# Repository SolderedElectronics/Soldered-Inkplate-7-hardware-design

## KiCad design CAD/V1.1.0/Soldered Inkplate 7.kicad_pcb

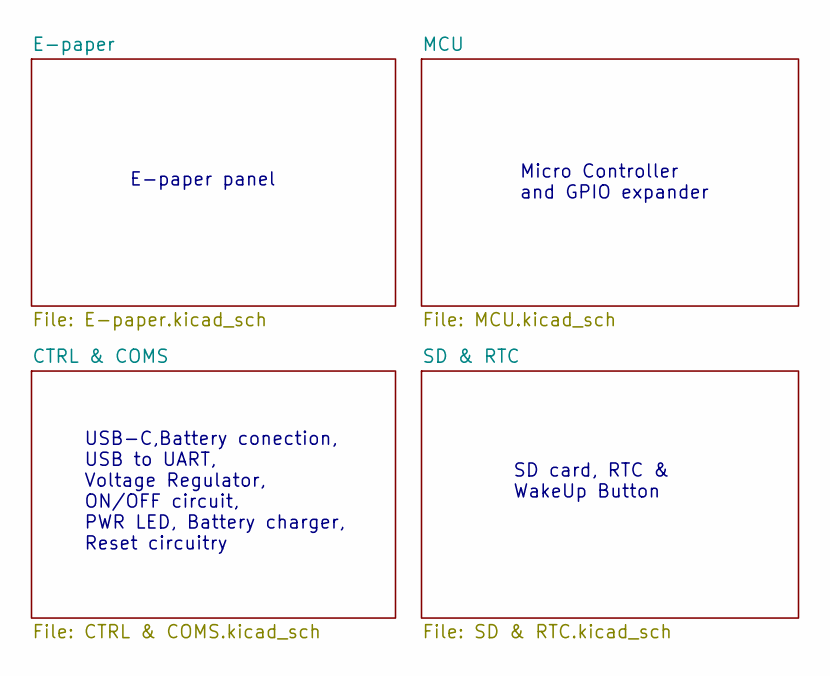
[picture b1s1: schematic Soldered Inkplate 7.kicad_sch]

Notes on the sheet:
E-paper panel
USB-C,Battery conection, USB to UART, Voltage Regulator, ON/OFF circuit, PWR LED, Battery charger, Reset circuitry
Micro Controller and GPIO expander
SD card, RTC & WakeUp Button

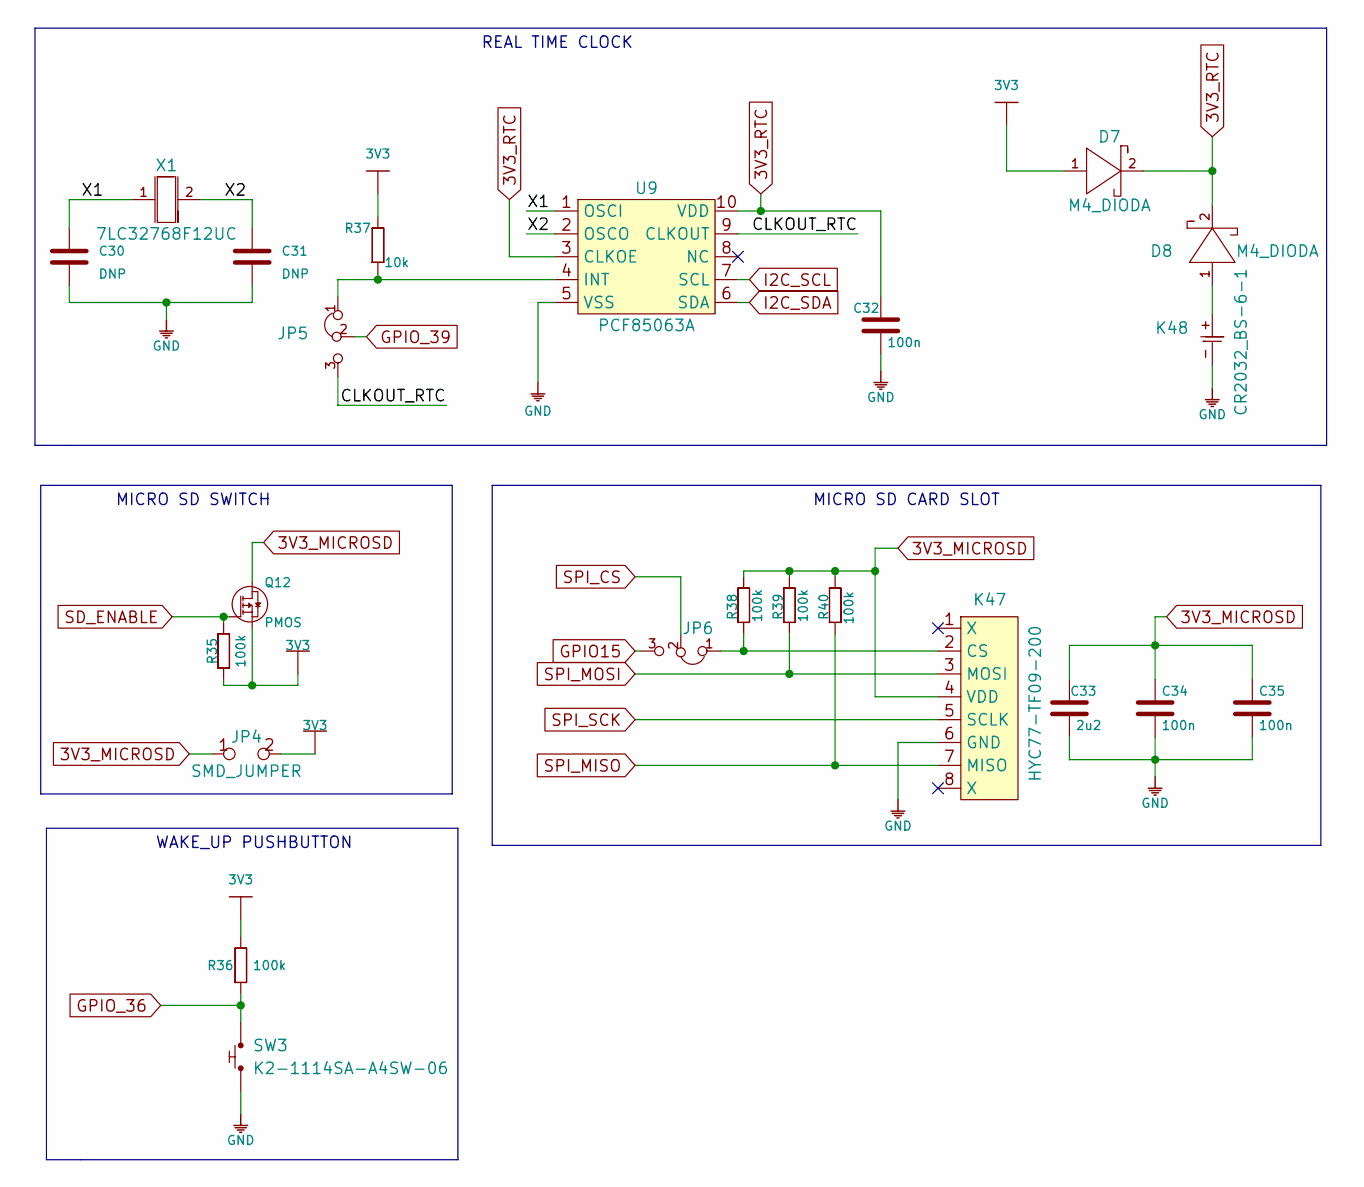
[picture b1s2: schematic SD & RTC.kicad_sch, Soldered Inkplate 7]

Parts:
C30, C31: DNP; 0603C
C32, C34, C35: 100n; 0603C
C33: 2u2; 0603C
D7, D8: M4_DIODA
JP4: SMD_JUMPER
JP5, JP6: SMD_JUMPER_3_PAD_CONNECTED_LEFT_TRACE
K47: HYC77-TF09-200
K48: CR2032_BS-6-1; CR2032-BS-6-1
Q12: PMOS; SOT-23-3
R35, R36, R38, R39, R40: 100k; 0603R
R37: 10k; 0603R
SW3: K2-1114SA-A4SW-06
U9: PCF85063A
X1: 7LC32768F12UC; ABS07AIG-32.768KHZ-7-D-T

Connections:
3V3: D7.1 (A), JP4.2, Q12.2 (S), R35.1, R36.2, R37.2; also elsewhere on the board
3V3_MICROSD: C33.2, C34.2, C35.2, JP4.1, K47.4 (VDD), Q12.3 (D), R38.2, R39.2, R40.2
3V3_RTC: C32.2, D7.2 (K), D8.2 (K), U9.3 (CLKOE), U9.10 (VDD)
/SD & RTC/CLKOUT_RTC: JP5.3, U9.9 (CLKOUT)
/SD & RTC/X1: C30.2, U9.1 (OSCI), X1.1
/SD & RTC/X2: C31.2, U9.2 (OSCO), X1.2
GND: C30.1, C31.1, C32.1, C33.1, C34.1, C35.1, K47.6 (GND), K48.-, SW3.1, U9.5 (VSS); also elsewhere on the board
GPIO15: JP6.3; also elsewhere on the board
GPIO_36: R36.1, SW3.2; also elsewhere on the board
GPIO_39: JP5.2; also elsewhere on the board
I2C_SCL: U9.7 (SCL); also elsewhere on the board
I2C_SDA: U9.6 (SDA); also elsewhere on the board
unnamed: D8.1 (A), K48.+
unnamed: JP5.1, R37.1, U9.4 (INT)
unnamed: JP6.1, K47.2 (CS), R38.1
SD_ENABLE: Q12.1 (G), R35.2; also elsewhere on the board
SPI_CS: JP6.2; also elsewhere on the board
SPI_MISO: K47.7 (MISO), R40.1; also elsewhere on the board
SPI_MOSI: K47.3 (MOSI), R39.1; also elsewhere on the board
SPI_SCK: K47.5 (SCLK); also elsewhere on the board

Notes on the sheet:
MICRO SD CARD SLOT
REAL TIME CLOCK
WAKE_UP PUSHBUTTON
MICRO SD SWITCH

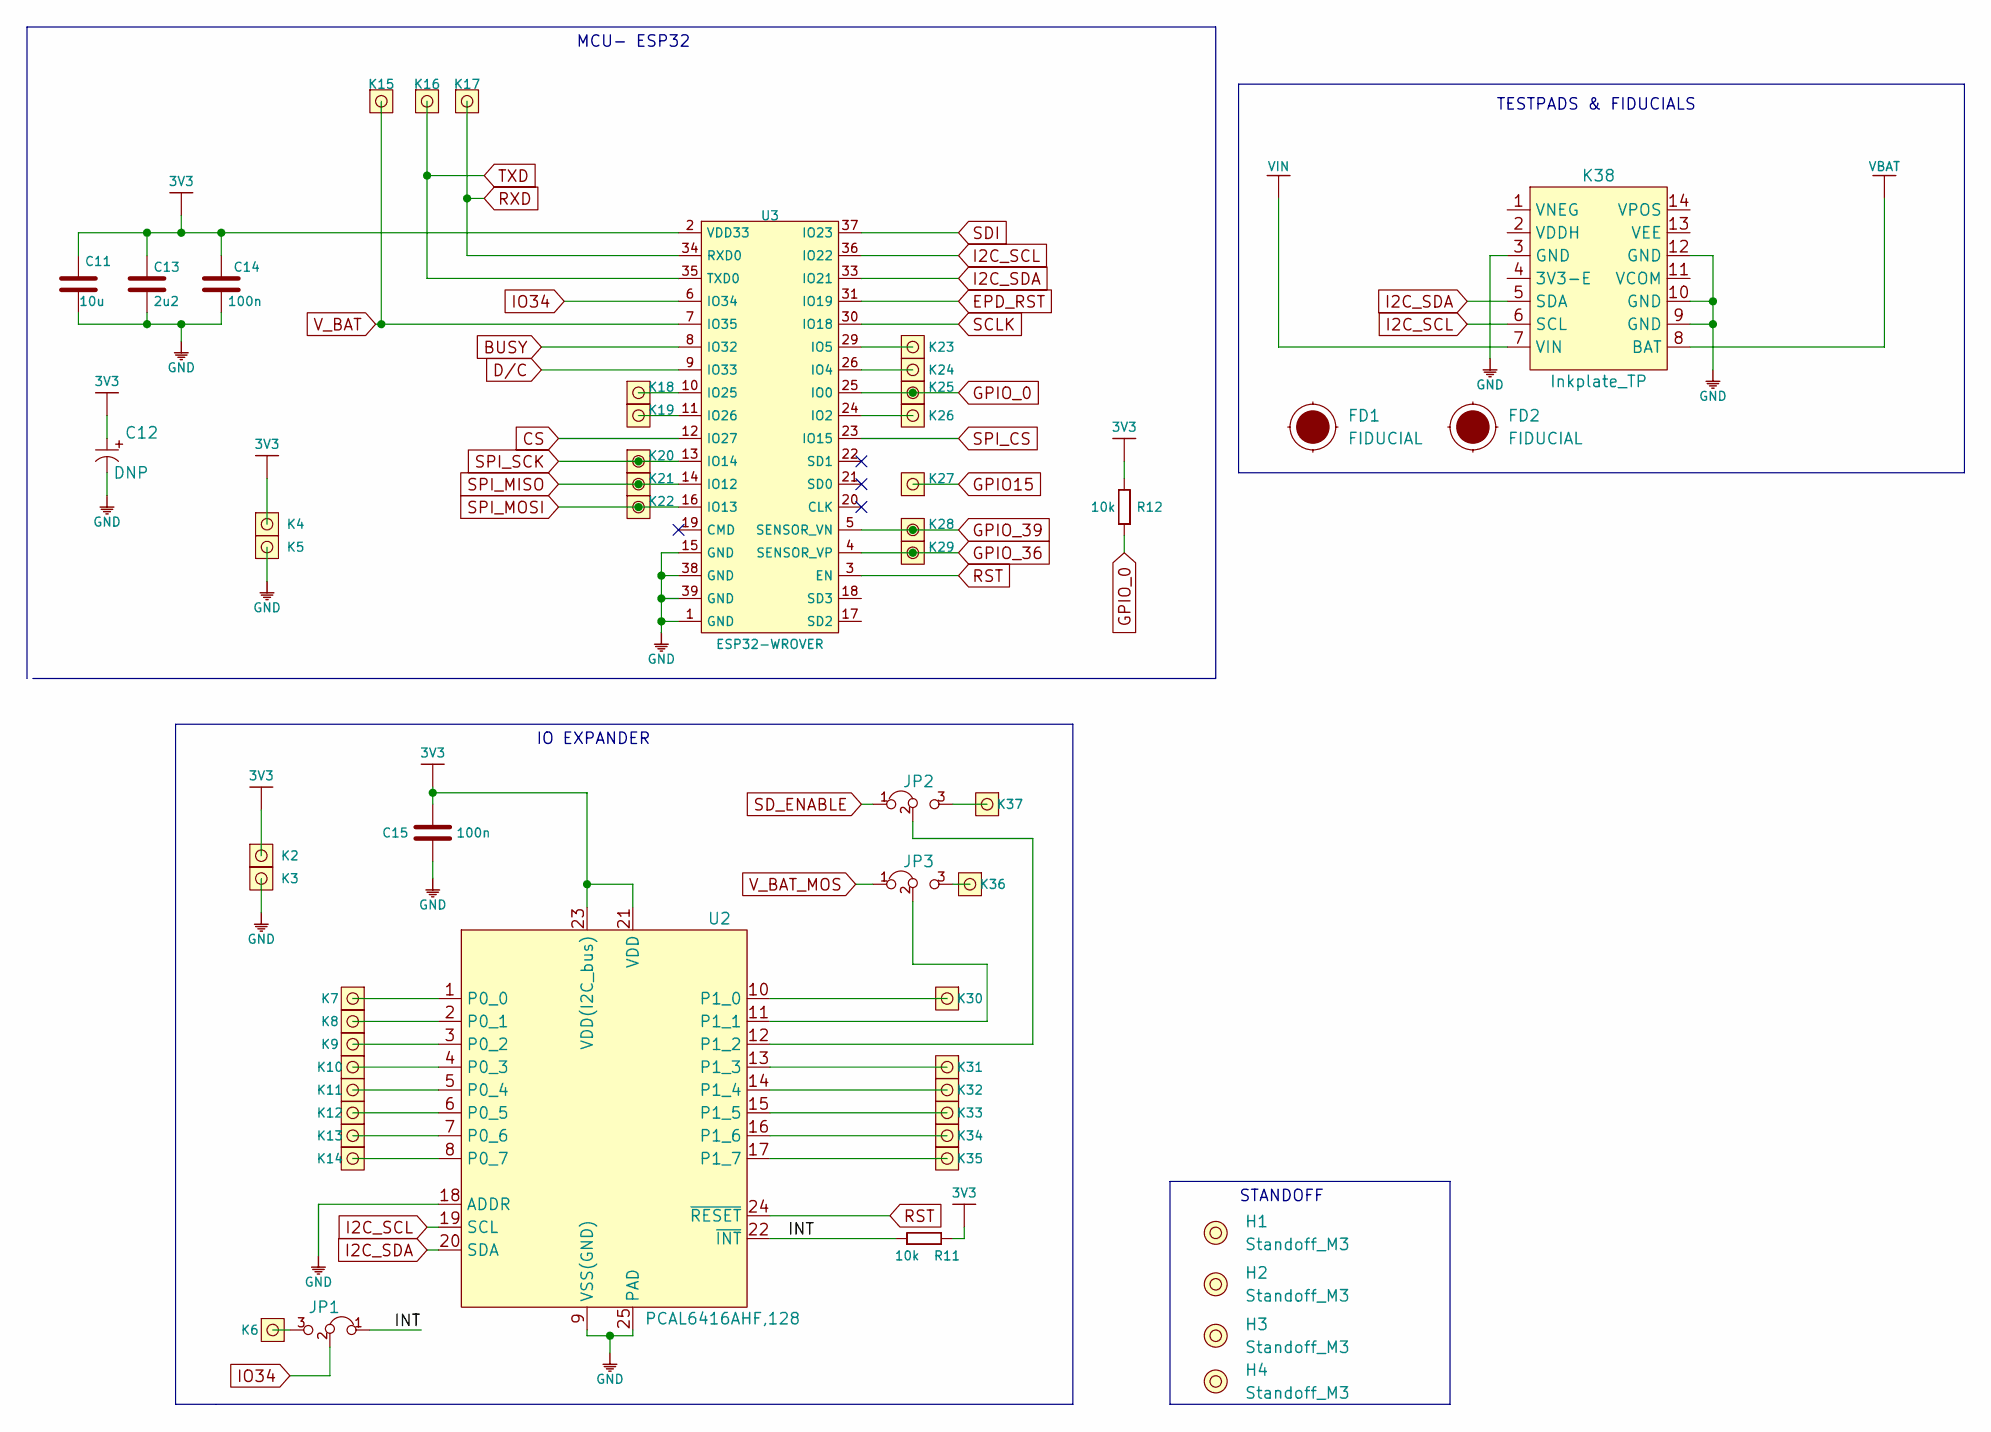
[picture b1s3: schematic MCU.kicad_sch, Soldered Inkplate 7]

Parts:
C11: 10u; 1206C
C12: DNP; 2917C
C13: 2u2; 0603C
C14, C15: 100n; 0603C
FD1, FD2: FIDUCIAL; FIDUCIAL_23
H1, H2, H3, H4: Standoff_M3
JP1, JP2, JP3: SMD_JUMPER_3_PAD_CONNECTED_LEFT_TRACE
K2, K3, K4, K5, K6, K7, K8, K9, K10, K11, K12, K13, K14, K15, K16, K17, K18, K19, K20, K21, K22, K23, K24, K25, K26, K27, K28, K29, K30, K31, K32, K33, K34, K35, K36, K37: HEADER_MALE_1X1_Inkplate
K38: Inkplate_TP; INKPLATE TEST HEADER
R11, R12: 10k; 0603R
U2: PCAL6416AHF,128
U3: ESP32-WROVER

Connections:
3V3: C11.2, C12.1 (+), C13.2, C14.2, C15.2, K2.1, K4.1, R11.1, R12.2, U2.21 (VDD), U2.23 (VDD(I2C_bus)), U3.2 (VDD33); also elsewhere on the board
/MCU/INT: JP1.1, R11.2, U2.22 (~INT)
BUSY: U3.8 (IO32); also elsewhere on the board
CS: U3.12 (IO27); also elsewhere on the board
D/C: U3.9 (IO33); also elsewhere on the board
EPD_RST: U3.31 (IO19); also elsewhere on the board
GND: C11.1, C12.2 (-), C13.1, C14.1, C15.1, K3.1, K5.1, K38.3 (GND), K38.9 (GND), K38.10 (GND), K38.12 (GND), U2.9 (VSS(GND)), U2.18 (ADDR), U2.25 (PAD), U3.1 (GND), U3.15 (GND), U3.38 (GND), U3.39 (GND); also elsewhere on the board
GPIO15: K27.1; also elsewhere on the board
GPIO_0: K25.1, R12.1, U3.25 (IO0); also elsewhere on the board
GPIO_36: K29.1, U3.4 (SENSOR_VP); also elsewhere on the board
GPIO_39: K28.1, U3.5 (SENSOR_VN); also elsewhere on the board
I2C_SCL: K38.6 (SCL), U2.19 (SCL), U3.36 (IO22); also elsewhere on the board
I2C_SDA: K38.5 (SDA), U2.20 (SDA), U3.33 (IO21); also elsewhere on the board
IO34: JP1.2, U3.6 (IO34)
unnamed: JP1.3, K6.1
unnamed: JP2.2, U2.12 (P1_2)
unnamed: JP2.3, K37.1
unnamed: JP3.2, U2.11 (P1_1)
unnamed: JP3.3, K36.1
unnamed: K7.1, U2.1 (P0_0)
unnamed: K8.1, U2.2 (P0_1)
unnamed: K9.1, U2.3 (P0_2)
unnamed: K10.1, U2.4 (P0_3)
unnamed: K11.1, U2.5 (P0_4)
unnamed: K12.1, U2.6 (P0_5)
unnamed: K13.1, U2.7 (P0_6)
unnamed: K14.1, U2.8 (P0_7)
unnamed: K18.1, U3.10 (IO25)
unnamed: K19.1, U3.11 (IO26)
unnamed: K23.1, U3.29 (IO5)
unnamed: K24.1, U3.26 (IO4)
unnamed: K26.1, U3.24 (IO2)
unnamed: K30.1, U2.10 (P1_0)
unnamed: K31.1, U2.13 (P1_3)
unnamed: K32.1, U2.14 (P1_4)
unnamed: K33.1, U2.15 (P1_5)
unnamed: K34.1, U2.16 (P1_6)
unnamed: K35.1, U2.17 (P1_7)
RST: U2.24 (~RESET), U3.3 (EN); also elsewhere on the board
RXD: K17.1, U3.34 (RXD0); also elsewhere on the board
SCLK: U3.30 (IO18); also elsewhere on the board
SDI: U3.37 (IO23); also elsewhere on the board
SD_ENABLE: JP2.1; also elsewhere on the board
SPI_CS: U3.23 (IO15); also elsewhere on the board
SPI_MISO: K21.1, U3.14 (IO12); also elsewhere on the board
SPI_MOSI: K22.1, U3.16 (IO13); also elsewhere on the board
SPI_SCK: K20.1, U3.13 (IO14); also elsewhere on the board
TXD: K16.1, U3.35 (TXD0); also elsewhere on the board
VBAT: K38.8 (BAT); also elsewhere on the board
VIN: K38.7 (VIN); also elsewhere on the board
V_BAT: K15.1, U3.7 (IO35); also elsewhere on the board
V_BAT_MOS: JP3.1; also elsewhere on the board

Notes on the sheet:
STANDOFF
IO EXPANDER
MCU- ESP32
TESTPADS & FIDUCIALS

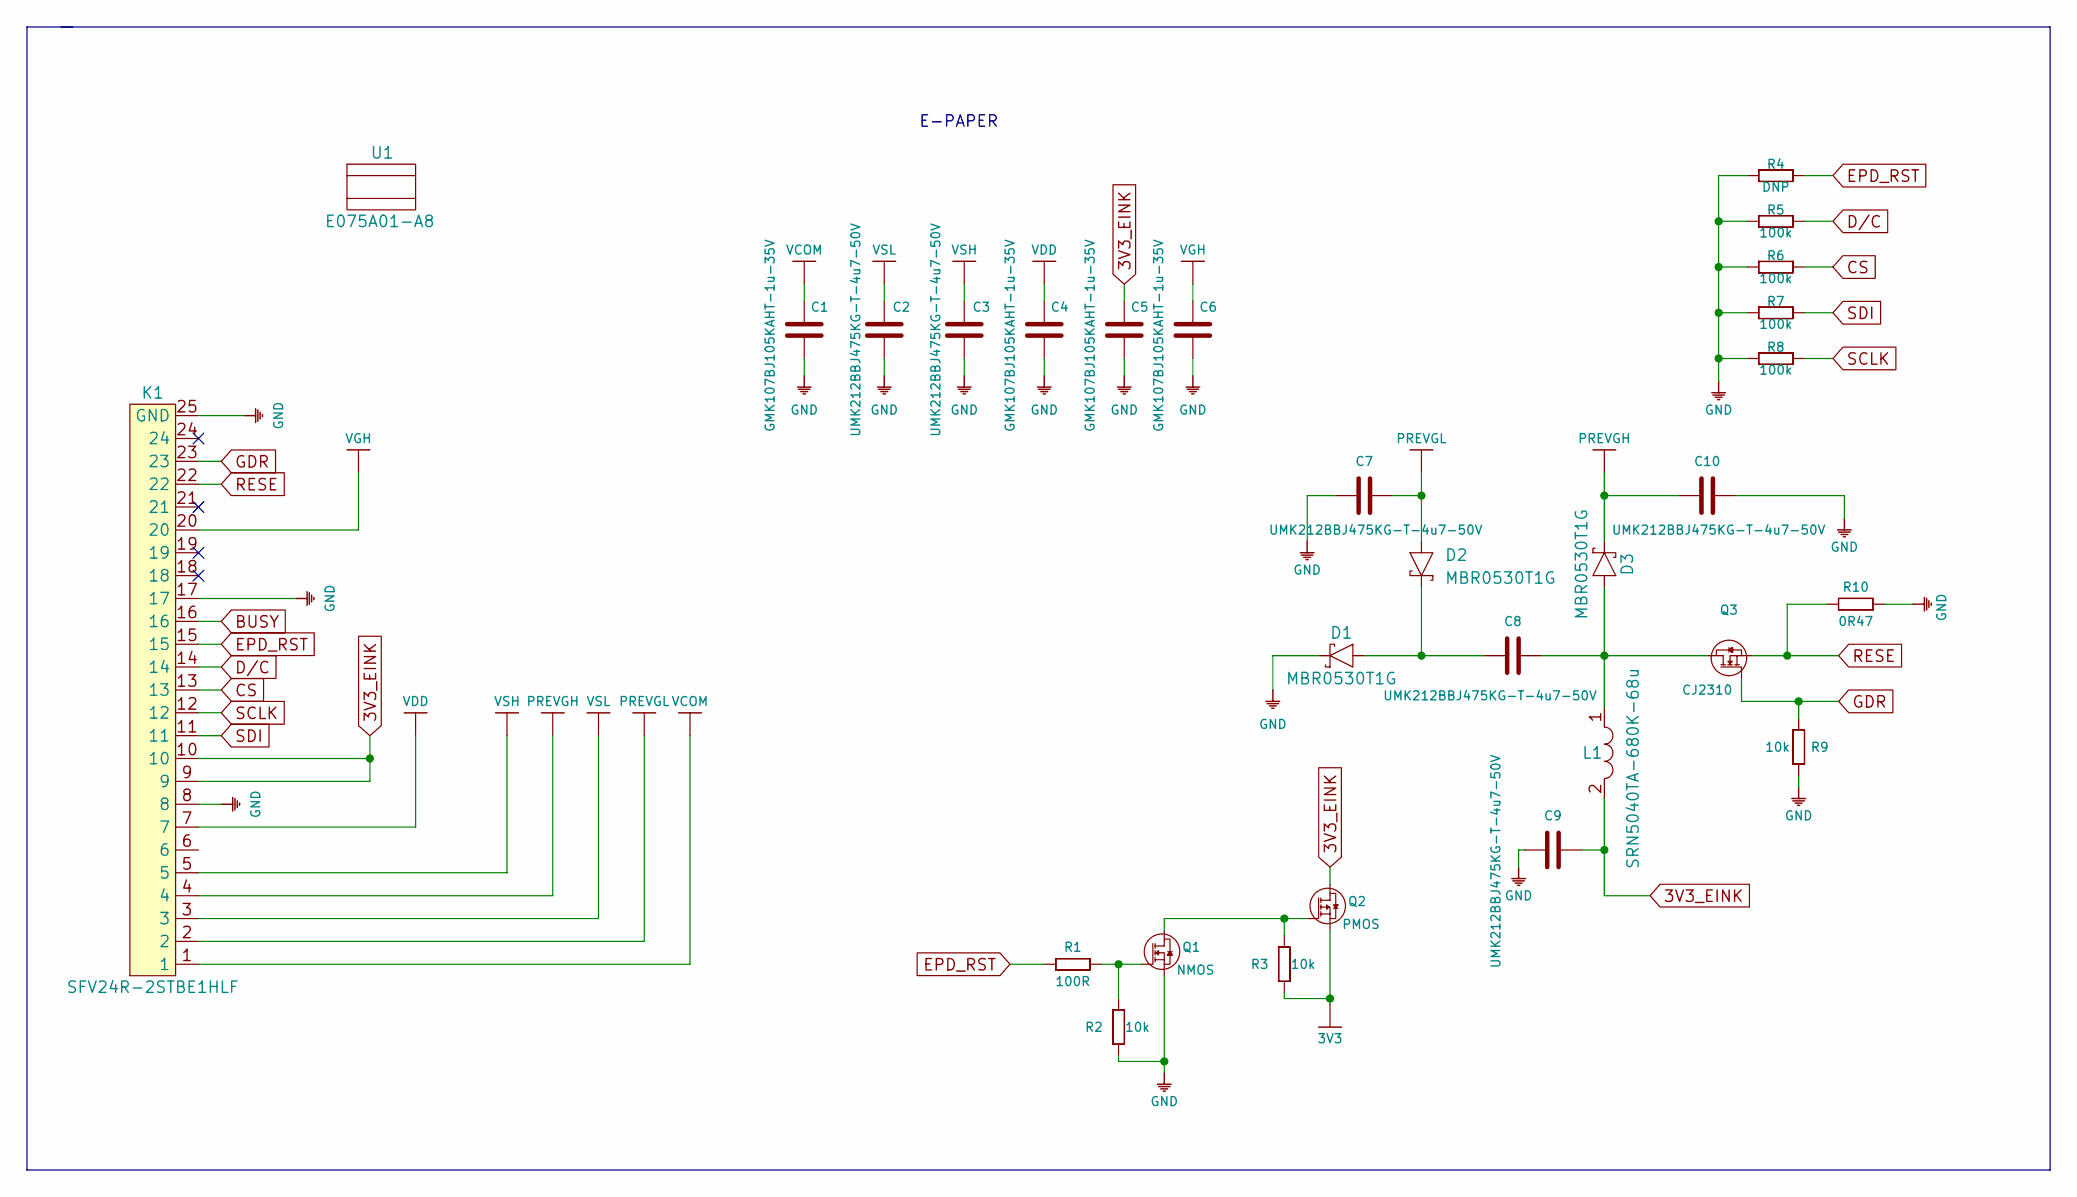
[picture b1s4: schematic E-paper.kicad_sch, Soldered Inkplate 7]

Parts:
C1, C4, C5, C6: GMK107BJ105KAHT-1u-35V; 0603C
C2, C3, C7, C8, C9, C10: UMK212BBJ475KG-T-4u7-50V; 0805C
D1, D2, D3: MBR0530T1G; SOD−123
K1: SFV24R-2STBE1HLF
L1: SRN5040TA-680K-68u; SRN5040TA-680K
Q1: NMOS; SOT-23-3
Q2: PMOS; SOT-23-3
Q3: CJ2310; SOT-23-3
R1: 100R; 0603R
R2, R3, R9: 10k; 0603R
R4: DNP; 0603R
R5, R6, R7, R8: 100k; 0603R
R10: 0R47; 0603R
U1: E075A01-A8

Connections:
3V3: Q2.2 (S), R3.1; also elsewhere on the board
3V3_EINK: C5.2, C9.2, K1.9, K1.10, L1.2, Q2.3 (D)
BUSY: K1.16; also elsewhere on the board
CS: K1.13, R6.2; also elsewhere on the board
D/C: K1.14, R5.2; also elsewhere on the board
EPD_RST: K1.15, R1.1, R4.2; also elsewhere on the board
GDR: K1.23, Q3.1 (G), R9.2
GND: C1.1, C2.1, C3.1, C4.1, C5.1, C6.1, C7.1, C9.1, C10.2, D1.1 (C), K1.8, K1.17, K1.25 (GND), Q1.2 (S), R2.1, R4.1, R5.1, R6.1, R7.1, R8.1, R9.1, R10.1; also elsewhere on the board
unnamed: C8.1, D1.2 (A), D2.1 (C)
unnamed: C8.2, D3.2 (A), L1.1, Q3.3 (D)
unnamed: Q1.1 (G), R1.2, R2.2
unnamed: Q1.3 (D), Q2.1 (G), R3.2
PREVGH: C10.1, D3.1 (C), K1.4
PREVGL: C7.2, D2.2 (A), K1.2
RESE: K1.22, Q3.2 (S), R10.2
SCLK: K1.12, R8.2; also elsewhere on the board
SDI: K1.11, R7.2; also elsewhere on the board
VCOM: C1.2, K1.1
VDD: C4.2, K1.7
VGH: C6.2, K1.20
VSH: C3.2, K1.5
VSL: C2.2, K1.3

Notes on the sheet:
E-PAPER

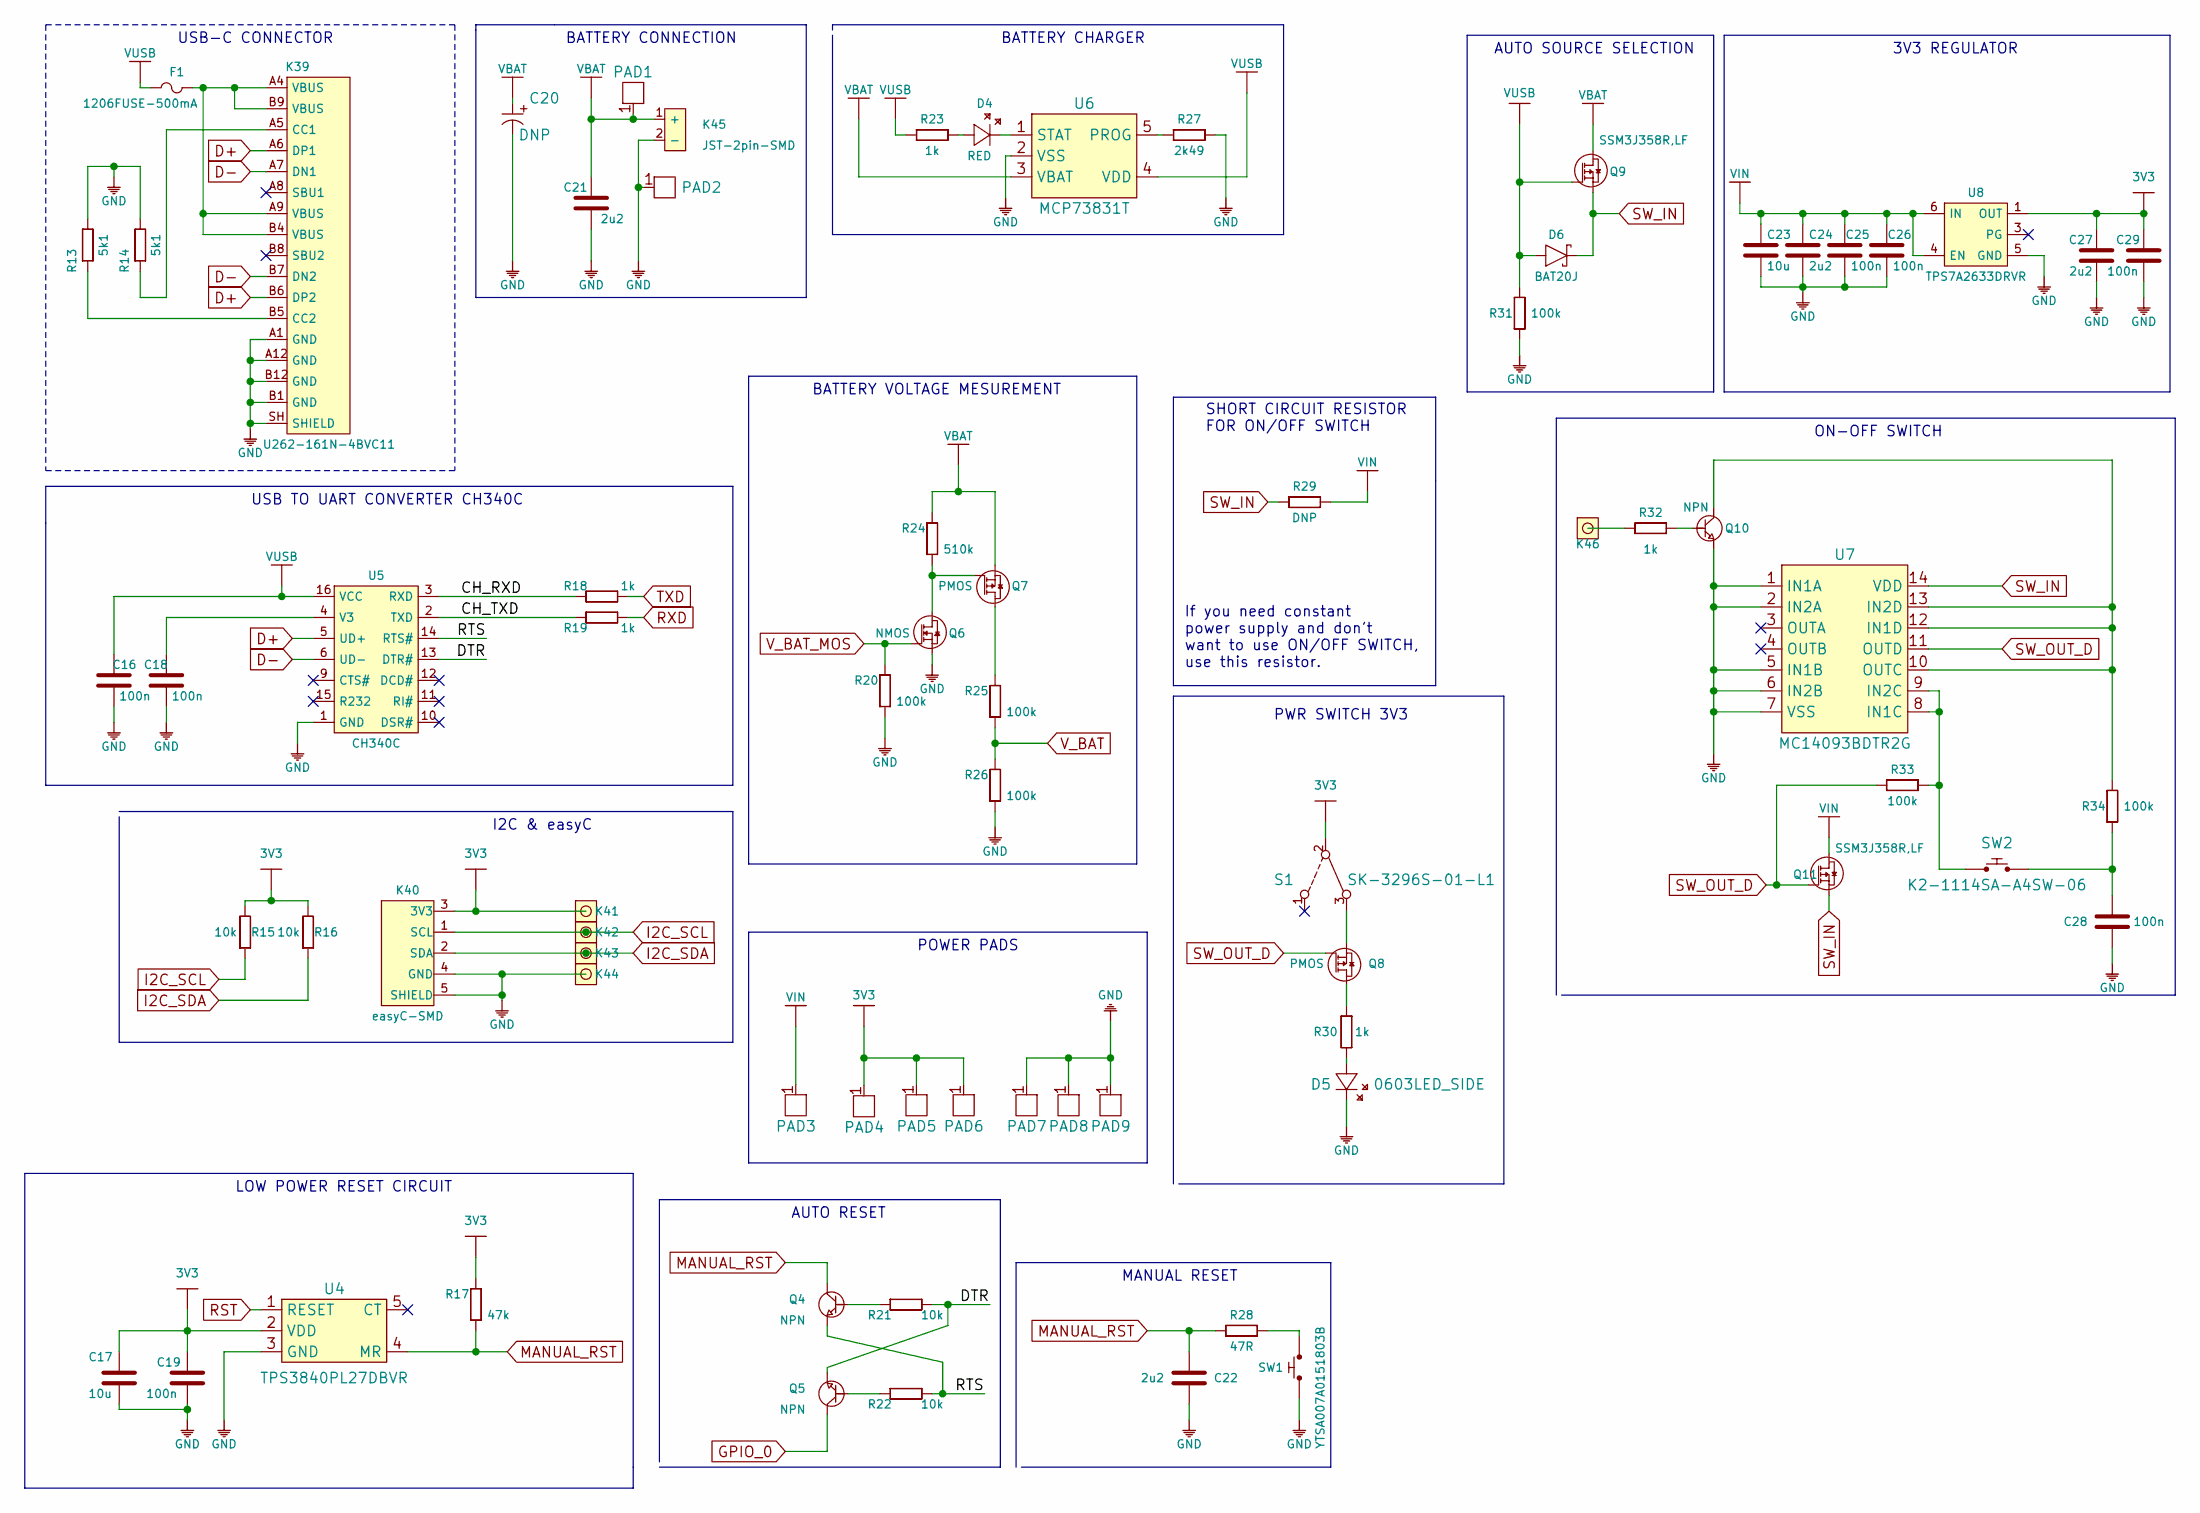
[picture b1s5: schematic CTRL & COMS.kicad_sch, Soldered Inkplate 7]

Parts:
C16, C18, C19, C25, C26, C28, C29: 100n; 0603C
C17, C23: 10u; 1206C
C20: DNP; 2917C
C21, C22, C24, C27: 2u2; 0603C
D4: RED; 0402LED
D5: 0603LED_SIDE; LTST-S270GKT
D6: BAT20J; SOD-323
F1: 1206FUSE-500mA; 1206FUSE
K39: U262-161N-4BVC11
K40: easyC-SMD; easyC-connector
K41, K42, K43, K44, K46: HEADER_MALE_1X1_Inkplate
K45: JST-2pin-SMD
PAD1, PAD2, PAD3, PAD4, PAD5, PAD6, PAD7, PAD8, PAD9: PAD_4x4
Q4, Q5, Q10: NPN; SOT-23-3
Q6: NMOS; SOT-23-3
Q7, Q8: PMOS; SOT-23-3
Q9, Q11: SSM3J358R,LF; SOT-23-3
R13, R14: 5k1; 0603R
R15, R16, R21, R22: 10k; 0603R
R17: 47k; 0603R
R18, R19, R23, R30, R32: 1k; 0603R
R20, R25, R26, R31, R33, R34: 100k; 0603R
R24: 510k; 0603R
R27: 2k49; 0603R
R28: 47R; 0603R
R29: DNP; 0603R
S1: SK-3296S-01-L1
SW1: YTSA007A0151803B
SW2: K2-1114SA-A4SW-06
U4: TPS3840PL27DBVR; SOT-23-5
U5: CH340C; SOP-16
U6: MCP73831T; SOT-23-5
U7: MC14093BDTR2G; TSSOP-14
U8: TPS7A2633DRVR

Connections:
3V3: C17.2, C19.2, C27.2, C29.2, K40.3 (3V3), K41.1, PAD4.1, PAD5.1, PAD6.1, R15.2, R16.2, R17.2, S1.2, U4.2 (VDD), U8.1 (OUT); also elsewhere on the board
/CTRL & COMS/CH_RXD: R18.1, U5.3 (RXD)
/CTRL & COMS/CH_TXD: R19.1, U5.2 (TXD)
/CTRL & COMS/DTR: Q5.2 (E), R21.2, U5.13 (DTR#)
/CTRL & COMS/RTS: Q4.2 (E), R22.2, U5.14 (RTS#)
D+: K39.A6 (DP1), K39.B6 (DP2), U5.5 (UD+)
D-: K39.A7 (DN1), K39.B7 (DN2), U5.6 (UD-)
GND: C16.1, C17.1, C18.1, C19.1, C20.2 (-), C21.1, C22.1, C23.1, C24.1, C25.1, C26.1, C27.1, C28.1, C29.1, D5.2 (K), K39.A1 (GND), K39.A12 (GND), K39.B1 (GND), K39.B12 (GND), K39.SH (SHIELD), K40.4 (GND), K40.5 (SHIELD), K44.1, K45.2 (-), PAD2.1, PAD7.1, PAD8.1, PAD9.1, Q6.2 (S), Q10.2 (E), R13.2, R14.2, R20.1, R26.1, R27.2, R31.1, SW1.1, U4.3 (GND), U5.1 (GND), U6.2 (VSS), U7.1 (IN1A), U7.2 (IN2A), U7.5 (IN1B), U7.6 (IN2B), U7.7 (VSS), U8.5 (GND); also elsewhere on the board
GPIO_0: Q5.3 (C); also elsewhere on the board
I2C_SCL: K40.1 (SCL), K42.1, R15.1; also elsewhere on the board
I2C_SDA: K40.2 (SDA), K43.1, R16.1; also elsewhere on the board
MANUAL_RST: C22.2, Q4.3 (C), R17.1, R28.2, U4.4 (MR)
unnamed: C18.2, U5.4 (V3)
unnamed: C28.2, R34.1, SW2.2
unnamed: D4.1 (A), R23.2
unnamed: D4.2 (K), U6.1 (STAT)
unnamed: D5.1 (A), R30.2
unnamed: F1.2, K39.A4 (VBUS), K39.A9 (VBUS), K39.B4 (VBUS), K39.B9 (VBUS)
unnamed: K39.A5 (CC1), R14.1
unnamed: K39.B5 (CC2), R13.1
unnamed: K46.1, R32.2
unnamed: Q4.1 (B), R21.1
unnamed: Q5.1 (B), R22.1
unnamed: Q6.3 (D), Q7.1 (G), R24.1
unnamed: Q7.3 (D), R25.2
unnamed: Q8.2 (S), S1.3
unnamed: Q8.3 (D), R30.1
unnamed: Q10.1 (B), R32.1
unnamed: Q10.3 (C), R34.2, U7.10 (OUTC), U7.12 (IN1D), U7.13 (IN2D)
unnamed: R27.1, U6.5 (PROG)
unnamed: R28.1, SW1.2
unnamed: R33.1, SW2.1, U7.8 (IN1C), U7.9 (IN2C)
RST: U4.1 (RESET); also elsewhere on the board
RXD: R19.2; also elsewhere on the board
SW_IN: D6.2 (C), Q9.2 (S), Q11.2 (S), R29.1, U7.14 (VDD)
SW_OUT_D: Q8.1 (G), Q11.1 (G), R33.2, U7.11 (OUTD)
TXD: R18.2; also elsewhere on the board
VBAT: C20.1 (+), C21.2, K45.1 (+), PAD1.1, Q7.2 (S), Q9.3 (D), R24.2, U6.3 (VBAT); also elsewhere on the board
VIN: C23.2, C24.2, C25.2, C26.2, PAD3.1, Q11.3 (D), R29.2, U8.4 (EN), U8.6 (IN); also elsewhere on the board
VUSB: C16.2, D6.1 (A), F1.1, Q9.1 (G), R23.1, R31.2, U5.16 (VCC), U6.4 (VDD)
V_BAT: R25.1, R26.2; also elsewhere on the board
V_BAT_MOS: Q6.1 (G), R20.2; also elsewhere on the board

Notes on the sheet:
PWR SWITCH 3V3
MANUAL RESET
3V3 REGULATOR
USB-C CONNECTOR
POWER PADS
LOW POWER RESET CIRCUIT
SHORT CIRCUIT RESISTOR FOR ON/OFF SWITCH
ON-OFF SWITCH
If you need constant power supply and don't want to use ON/OFF SWITCH, use this resistor.
I2C & easyC
USB TO UART CONVERTER CH340C
BATTERY VOLTAGE MESUREMENT
AUTO SOURCE SELECTION
AUTO RESET
BATTERY CONNECTION
BATTERY CHARGER

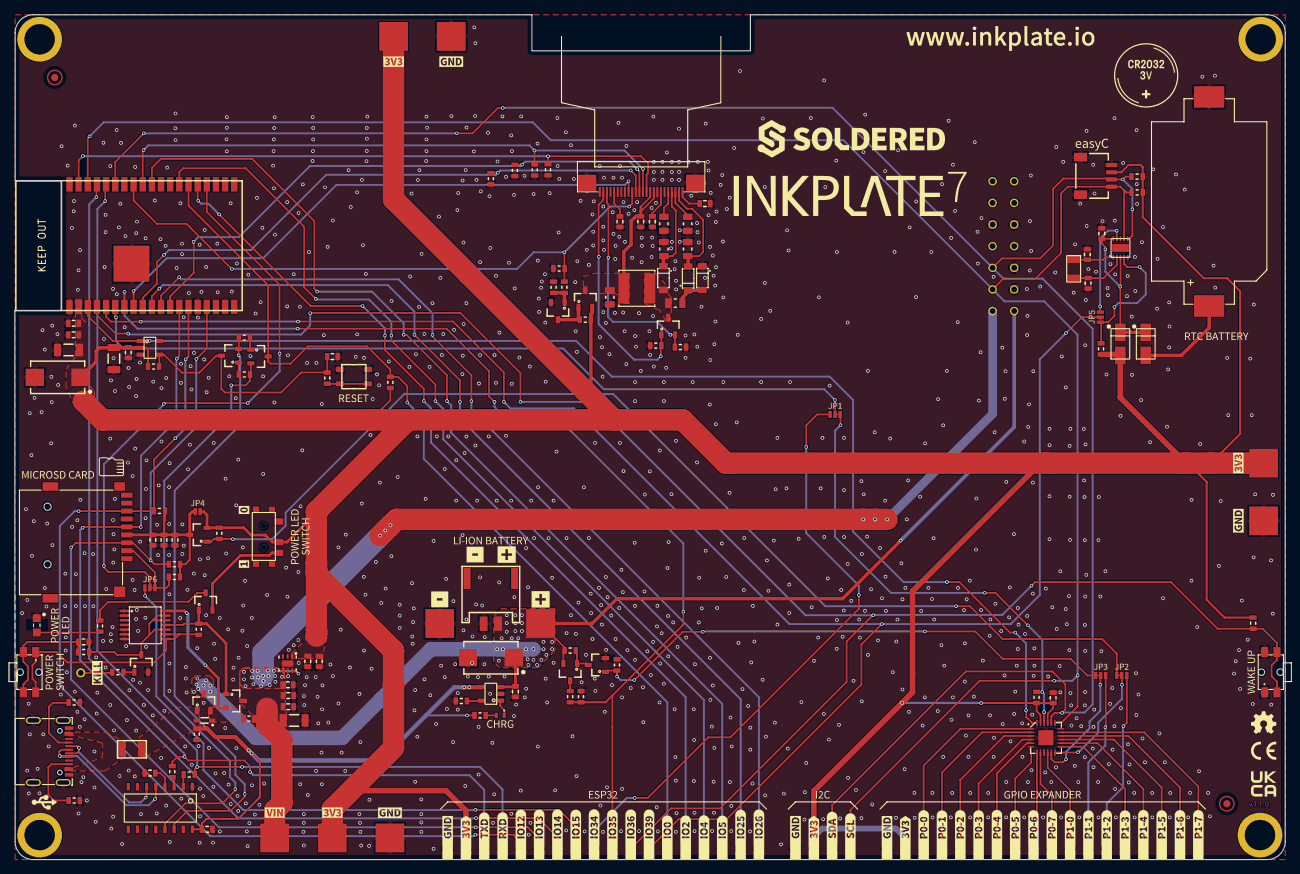
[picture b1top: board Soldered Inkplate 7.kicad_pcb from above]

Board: 2 copper layers, 176.2 x 117.2 mm, 257 parts (1 on the bottom side), 104 nets.

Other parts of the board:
Ref**: Val**; Version1.1.0
kibuzzard-63FC5BF8: G***; kibuzzard-63FC5BF8
kibuzzard-63FC5C0F: G***; kibuzzard-63FC5C0F
kibuzzard-63FC5C1D: G***; kibuzzard-63FC5C1D
kibuzzard-63FC5C04: G***; kibuzzard-63FC5C04
kibuzzard-63FC5C4F: G***; kibuzzard-63FC5C4F
kibuzzard-63FC5C5F: G***; kibuzzard-63FC5C5F
kibuzzard-63FC5C6B: G***; kibuzzard-63FC5C6B
kibuzzard-63FC5C7E: G***; kibuzzard-63FC5C7E
kibuzzard-63FC5C9A: G***; kibuzzard-63FC5C9A
kibuzzard-63FC5C17: G***; kibuzzard-63FC5C17
kibuzzard-63FC5C40: G***; kibuzzard-63FC5C40
kibuzzard-63FC5C46: G***; kibuzzard-63FC5C46
kibuzzard-63FC5C65: G***; kibuzzard-63FC5C65
kibuzzard-63FC5C84: G***; kibuzzard-63FC5C84
kibuzzard-63FC5C93: G***; kibuzzard-63FC5C93
kibuzzard-63FC5CA4: G***; kibuzzard-63FC5CA4
kibuzzard-63FC5CB5: G***; kibuzzard-63FC5CB5
kibuzzard-63FC5CBB: G***; kibuzzard-63FC5CBB
kibuzzard-63FC5CCD: G***; kibuzzard-63FC5CCD
kibuzzard-63FC5CD4: G***; kibuzzard-63FC5CD4
kibuzzard-63FC5CDA: G***; kibuzzard-63FC5CDA
kibuzzard-63FC5CE4: G***; kibuzzard-63FC5CE4
kibuzzard-63FC5CF6: G***; kibuzzard-63FC5CF6
kibuzzard-63FC5CFE: G***; kibuzzard-63FC5CFE
kibuzzard-63FC5D5D: G***; kibuzzard-63FC5D5D
kibuzzard-63FC5D6B: G***; kibuzzard-63FC5D6B
kibuzzard-63FC5D09: G***; kibuzzard-63FC5D09
kibuzzard-63FC5D13: G***; kibuzzard-63FC5D13
kibuzzard-63FC5D43: G***; kibuzzard-63FC5D43
kibuzzard-63FC5D64: G***; kibuzzard-63FC5D64
kibuzzard-63FC5D72: G***; kibuzzard-63FC5D72
kibuzzard-63FC5D84: G***; kibuzzard-63FC5D84
kibuzzard-63FC5D91: G***; kibuzzard-63FC5D91
kibuzzard-63FC5F9D: G***; kibuzzard-63FC5F9D
kibuzzard-63FC5F93: G***; kibuzzard-63FC5F93
kibuzzard-63FC5FB3: G***; kibuzzard-63FC5FB3
kibuzzard-63FC5FC1: G***; kibuzzard-63FC5FC1
kibuzzard-63FC5FCF: G***; kibuzzard-63FC5FCF
kibuzzard-63FC5FEC: G***; kibuzzard-63FC5FEC
kibuzzard-63FC5FF3: G***; kibuzzard-63FC5FF3
kibuzzard-63FC60AD: G***; kibuzzard-63FC60AD
kibuzzard-63FC60BC: G***; kibuzzard-63FC60BC
kibuzzard-63FC60D1: G***; kibuzzard-63FC60D1
kibuzzard-63FC60DF: G***; kibuzzard-63FC60DF
kibuzzard-63FC60EF: G***; kibuzzard-63FC60EF
kibuzzard-63FC60FE: G***; kibuzzard-63FC60FE
kibuzzard-63FC604C: G***; kibuzzard-63FC604C
kibuzzard-63FC605A: G***; kibuzzard-63FC605A
kibuzzard-63FC607B: G***; kibuzzard-63FC607B
kibuzzard-63FC609F: G***; kibuzzard-63FC609F
kibuzzard-63FC610B: G***; kibuzzard-63FC610B
kibuzzard-63FC6004: G***; kibuzzard-63FC6004
kibuzzard-63FC6015: G***; kibuzzard-63FC6015
kibuzzard-63FC6024: G***; kibuzzard-63FC6024
kibuzzard-63FC6033: G***; kibuzzard-63FC6033
kibuzzard-63FC6069: G***; kibuzzard-63FC6069
kibuzzard-63FC6091: G***; kibuzzard-63FC6091
kibuzzard-63FC6216: G***; kibuzzard-63FC6216
kibuzzard-63FEEEE7: G***; kibuzzard-63FEEEE7
kibuzzard-63FEEEF4: G***; kibuzzard-63FEEEF4
kibuzzard-63FEEF1F: G***; kibuzzard-63FEEF1F
kibuzzard-63FEEF2B: G***; kibuzzard-63FEEF2B
kibuzzard-63FEEF5E: G***; kibuzzard-63FEEF5E
kibuzzard-63FEEF07: G***; kibuzzard-63FEEF07
kibuzzard-63FEEF7E: G***; kibuzzard-63FEEF7E
kibuzzard-63FEEF9D: G***; kibuzzard-63FEEF9D
kibuzzard-63FEEF14: G***; kibuzzard-63FEEF14
kibuzzard-63FEEF39: G***; kibuzzard-63FEEF39
kibuzzard-63FEEF46: G***; kibuzzard-63FEEF46
kibuzzard-63FEEF51: G***; kibuzzard-63FEEF51
kibuzzard-63FEEF74: G***; kibuzzard-63FEEF74
kibuzzard-63FEEF89: G***; kibuzzard-63FEEF89
kibuzzard-63FEEF93: G***; kibuzzard-63FEEF93
kibuzzard-63FEEFA7: G***; kibuzzard-63FEEFA7
kibuzzard-63FEEFB2: G***; kibuzzard-63FEEFB2
kibuzzard-63FEEFBC: G***; kibuzzard-63FEEFBC

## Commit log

2024-10-20 Updating open source files.
